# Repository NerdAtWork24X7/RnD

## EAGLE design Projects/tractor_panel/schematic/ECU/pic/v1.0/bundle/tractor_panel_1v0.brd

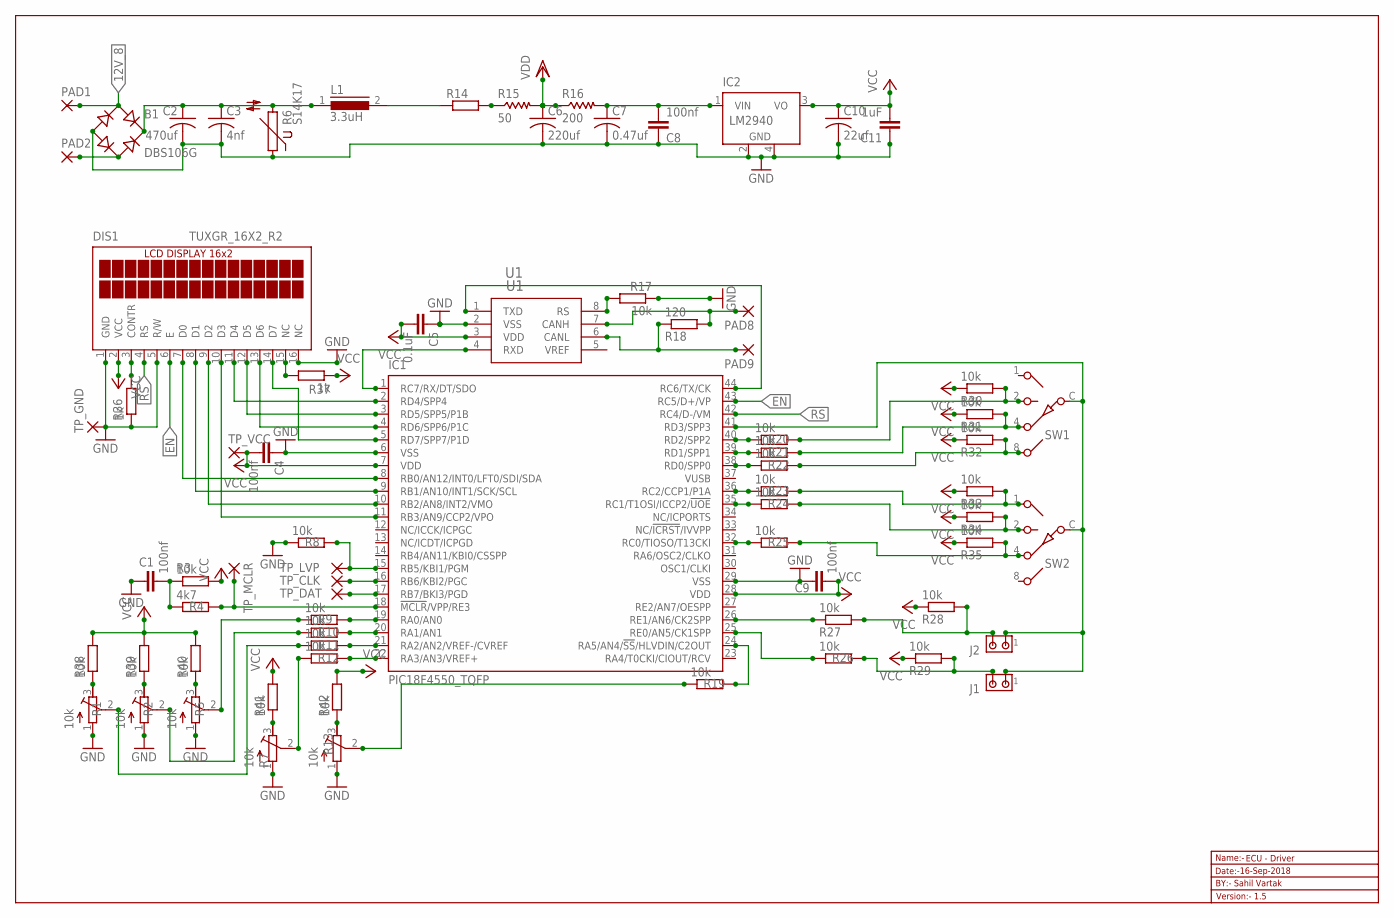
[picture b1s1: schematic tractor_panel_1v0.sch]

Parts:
B1: DBS106G; DBS
C1, C4, C8, C9: 100nf; C0603
C2: 470uf; C050-075X075
C3: 4nf; C050-045X075
C5: 0.1uF; C0603
C6: 220uf; C025-025X050
C7: 0.47uf; C025-025X050
C10: 22uf; C025-025X050
C11: 1uF; C0603
DIS1: TUXGR_16X2_R2
IC1: PIC18F4550_TQFP; TQFP44
IC2: LM2940; SOT223
J1, J2: MTA02-156; 1X2MTA
L1: 3.3uH; 82114R
PAD1, PAD2, PAD8, PAD9: 2,54/1,1
R1, R2, R5, R7, R13: 10k; RTRIM3296W
R3, R8, R9, R10, R11, R12, R17, R19, R20, R21, R22, R23, R24, R25, R26, R27, R28, R29, R30, R31, R32, R33, R34, R35, R38, R39, R40, R41, R42: 10k; R0603
R4: 4k7; R0603
R6: S14K17
R14: R-EU_R0603; R0603
R15: 50; WSC2515
R16: 200; WSC2515
R18: 120; R0603
R36, R37: 1k; R0603
SW1, SW2: SW-C10
TP_CLK: 1,6/0,8
TP_DAT: 1,6/0,8
TP_GND: 1,6/0,8
TP_LVP: 1,6/0,8
TP_MCLR: 1,6/0,8
TP_VCC: 1,6/0,8
U1: U1; SOIC8-N_MC-M

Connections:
12V_8: B1.AC1, PAD1.1
EN: DIS1.6 (E), IC1.43 (RC5/D+/VP)
GND: B1.-, C1.1, C2.2, C3.2, C4.1, C5.1, C6.2, C7.2, C8.1, C9.1, C10.2, C11.1, DIS1.1 (GND), DIS1.5 (R/W), DIS1.16 (NC), IC1.6 (VSS), IC1.29 (VSS), IC2.2 (GND), IC2.4 (GND), R1.1 (A), R2.1 (A), R5.1 (A), R6.1, R7.1 (A), R8.1, R13.1 (A), R17.1, R36.1, TP_GND.1, U1.2 (VSS)
unnamed: B1.AC2, PAD2.1
unnamed: DIS1.7 (D0), IC1.8 (RB0/AN12/INT0/LFT0/SDI/SDA)
unnamed: L1.2, R14.1
unnamed: DIS1.8 (D1), IC1.9 (RB1/AN10/INT1/SCK/SCL)
unnamed: R13.2 (S), R19.1
unnamed: DIS1.9 (D2), IC1.10 (RB2/AN8/INT2/VMO)
unnamed: C7.1, C8.2, IC2.1 (VIN), R16.2
unnamed: DIS1.3 (CONTR), R36.2
unnamed: DIS1.15 (NC), R37.2
unnamed: DIS1.10 (D3), IC1.11 (RB3/AN9/CCP2/VPO)
unnamed: DIS1.11 (D4), IC1.2 (RD4/SPP4)
unnamed: DIS1.14 (D7), IC1.5 (RD7/SPP7/P1D)
unnamed: R1.3 (E), R38.1
unnamed: R2.3 (E), R39.1
unnamed: R14.2, R15.1
unnamed: R5.3 (E), R40.1
unnamed: R7.3 (E), R41.1
unnamed: R13.3 (E), R42.1
unnamed: IC1.41 (RD3/SPP3), J1.1, J2.1, SW1.C, SW2.C
unnamed: B1.+, C2.1, C3.1, L1.1, R6.2
unnamed: DIS1.13 (D6), IC1.4 (RD6/SPP6/P1C)
unnamed: DIS1.12 (D5), IC1.3 (RD5/SPP5/P1B)
unnamed: PAD9.1, R18.1, U1.6 (CANL)
unnamed: PAD8.1, R18.2, U1.7 (CANH)
unnamed: IC1.1 (RC7/RX/DT/SDO), U1.4 (RXD)
unnamed: IC1.44 (RC6/TX/CK), U1.1 (TXD)
unnamed: R17.2, U1.8 (RS)
unnamed: J2.2, R27.2, R28.2
unnamed: IC1.26 (RE1/AN6/CK2SPP), R27.1
unnamed: IC1.32 (RC0/TIOSO/T13CKI), R25.1
unnamed: IC1.35 (RC1/T1OSI/ICCP2/!UOE), R24.1
unnamed: IC1.36 (RC2/CCP1/P1A), R23.1
unnamed: IC1.38 (RD0/SPP0), R22.1
unnamed: IC1.39 (RD1/SPP1), R21.1
unnamed: IC1.40 (RD2/SPP2), R20.1
unnamed: R20.2, R30.2, SW1.2
unnamed: R21.2, R31.2, SW1.4
unnamed: R22.2, R32.2, SW1.8
unnamed: R23.2, R33.2, SW2.1
unnamed: R24.2, R34.2, SW2.2
unnamed: R25.2, R35.2, SW2.4
unnamed: IC1.25 (RE0/AN5/CK1SPP), R26.1
unnamed: IC1.17 (RB7/BKI3/PGD), TP_DAT.1
unnamed: IC1.16 (RB6/KBI2/PGC), TP_CLK.1
unnamed: J1.2, R26.2, R29.2
unnamed: IC1.22 (RA3/AN3/VREF+), R12.2
unnamed: IC1.21 (RA2/AN2/VREF-/CVREF), R11.2
unnamed: IC1.20 (RA1/AN1), R10.2
unnamed: IC1.19 (RA0/AN0), R9.2
unnamed: R5.2 (S), R9.1
unnamed: R2.2 (S), R10.1
unnamed: R1.2 (S), R11.1
unnamed: R7.2 (S), R12.1
unnamed: IC1.24 (RA5/AN4/!SS!/HLVDIN/C2OUT), R19.2
unnamed: C1.2, R3.1, R4.1
unnamed: IC1.18 (!MCLR!/VPP/RE3), R4.2, TP_MCLR.1
unnamed: IC1.15 (RB5/KBI1/PGM), R8.2, TP_LVP.1
RS: DIS1.4 (RS), IC1.42 (RC4/D-/VM)
VCC: C4.2, C5.2, C9.2, C10.1, C11.2, DIS1.2 (VCC), IC1.7 (VDD), IC1.28 (VDD), IC2.3 (VO), R3.2, R28.1, R29.1, R30.1, R31.1, R32.1, R33.1, R34.1, R35.1, R37.1, R38.2, R39.2, R40.2, R41.2, R42.2, TP_VCC.1, U1.3 (VDD)
VDD: C6.1, R15.2, R16.1

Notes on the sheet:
Name:-
Version:- 1.5
Date:-
ECU - Driver
BY:- Sahil Vartak
16-Sep-2018

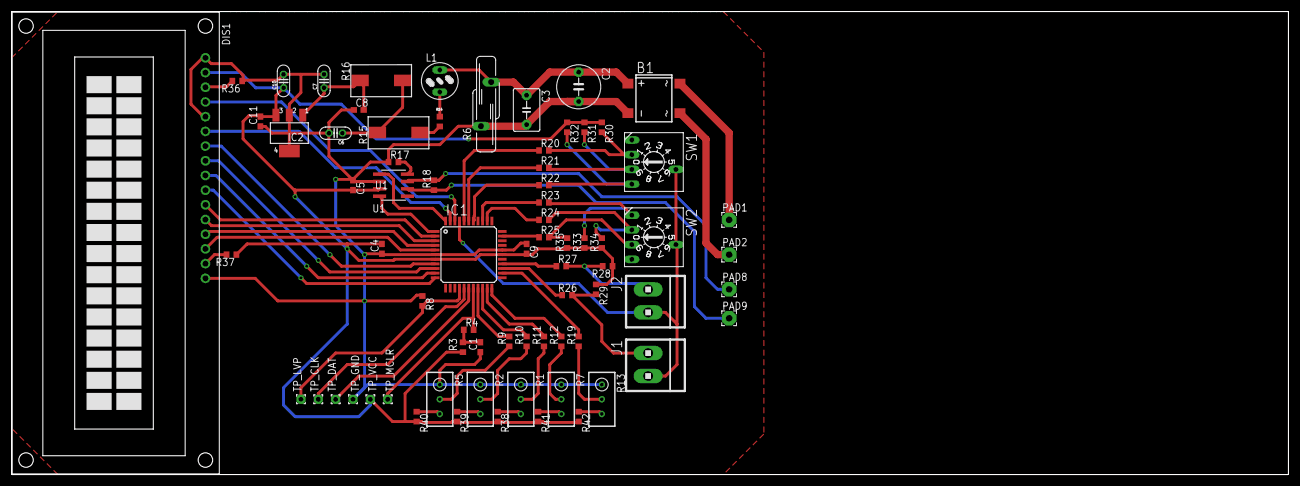
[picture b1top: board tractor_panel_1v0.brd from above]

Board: 2 copper layers, 220.7 x 80.0 mm, 73 parts (0 on the bottom side), 63 nets.

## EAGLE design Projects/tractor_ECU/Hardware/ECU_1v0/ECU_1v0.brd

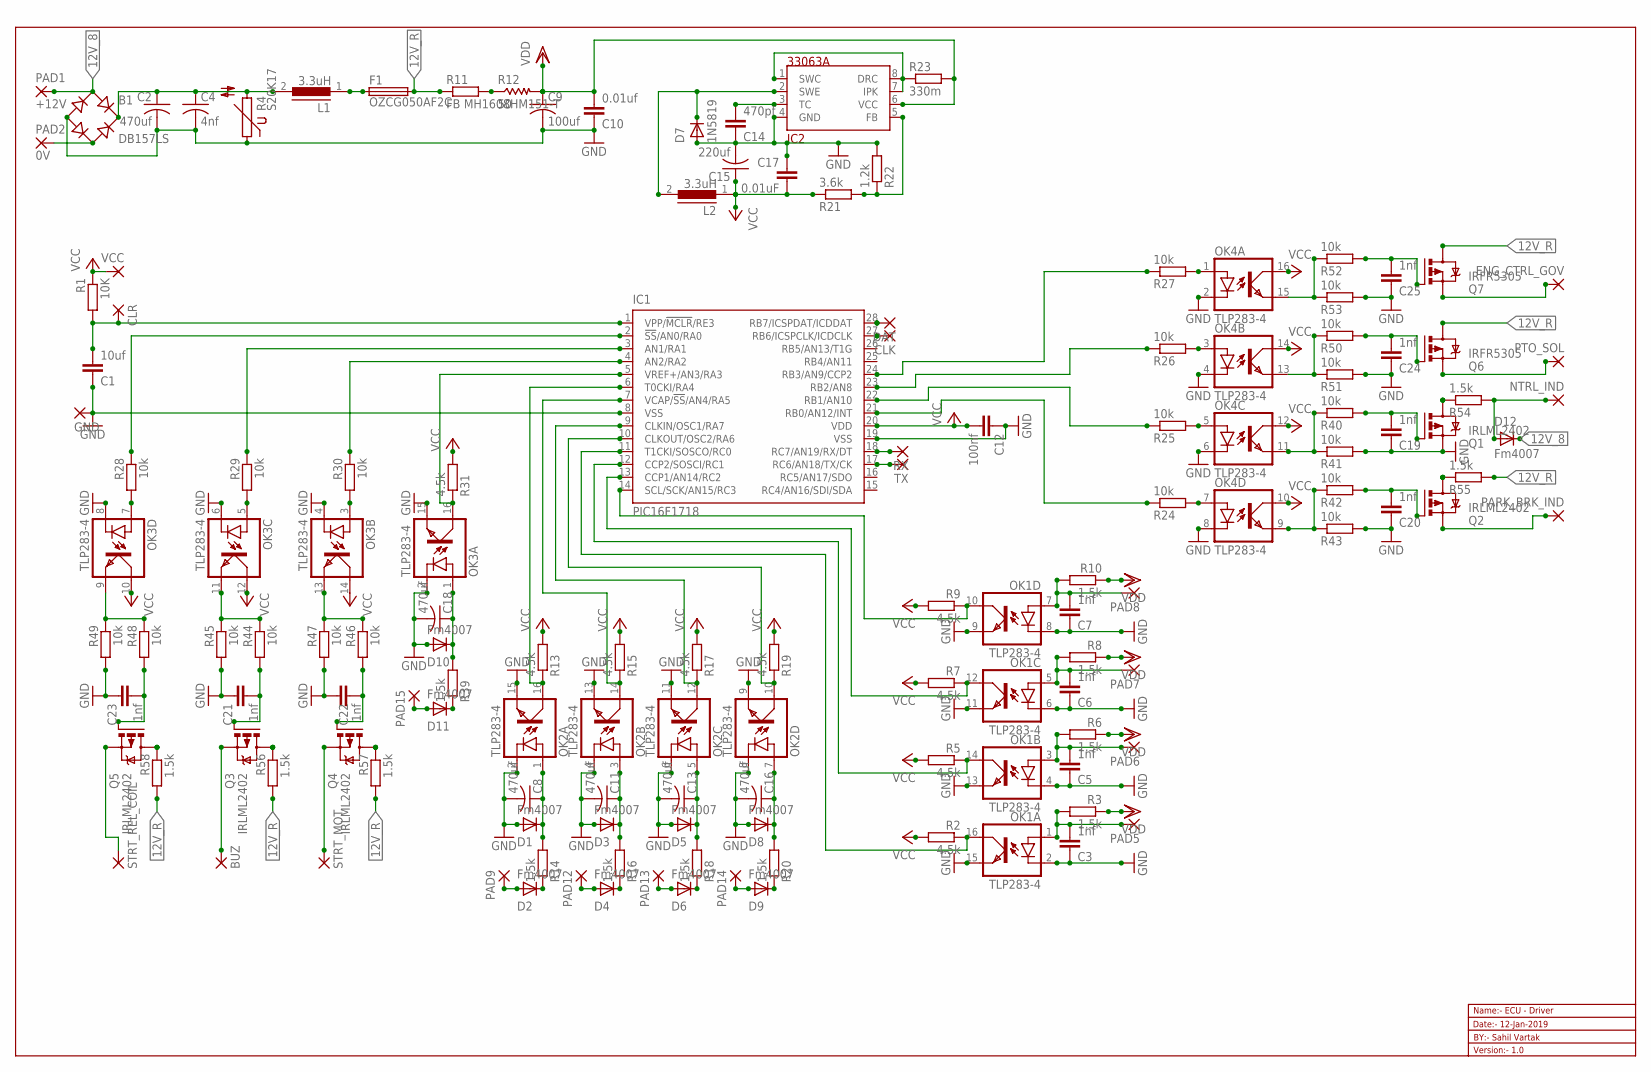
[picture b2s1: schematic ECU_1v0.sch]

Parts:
B1: DB157LS; DBS
BUZ: 2,54/1,1
C1: 10uf; C0603
C2, C8, C11, C13, C16, C18: 470uf; C050-075X075
C3, C5, C6, C7, C19, C20, C21, C22, C23, C24, C25: 1nf; C0603
C4: 4nf; C050-045X075
C9: 100uf; C025-025X050
C10: 0.01uf; C0603
C12: 100nf; C0603
C14: 470pf; C0603
C15: 220uf; C025-025X050
C17: 0.01uF; C0603
CLK: 1,6/0,8
CLR: 1,6/0,8
D1, D2, D3, D4, D5, D6, D8, D9, D10, D11, D12: Fm4007; SMA-DO214AC
D7: 1N5819; SMA-DO214AC
DAT: 1,6/0,8
ENG_CTRL_GOV: 2,54/1,1
F1: OZCG050AF2C; RES_FUSE
GND: 1,6/0,8
IC1: PIC16F1718; SO28W
IC2: 33063A; D_R-PDSO-G8
L1, L2: 3.3uH; 82114R
NTRL_IND: 2,54/1,1
OK1, OK2, OK3, OK4: TLP283-4; MINI-FLAT-16
PAD1: +12V; 2,54/1,1
PAD2: 0V; 2,54/1,1
PAD5, PAD6, PAD7, PAD8, PAD9, PAD12, PAD13, PAD14, PAD15: 2,54/1,1
PARK_BRK_IND: 2,54/1,1
PTO_SOL: 2,54/1,1
Q1, Q2, Q3, Q4, Q5: IRLML2402; MICRO3
Q6, Q7: IRFR5305; D-PAK_TO252AA
R1: 10K; R0603
R2, R5, R7, R9, R13, R15, R17, R19, R31: 4.5k; R0603
R3, R6, R8, R10, R14, R16, R18, R20, R39, R54, R55, R56, R57, R58: 1.5k; R0603
R4: S20K17; S14K17
R11: FB MH1608HM151-T; R0603
R12: 50; WSC2515
R21: 3.6k; R0603
R22: 1.2k; R0603
R23: 330m; R2010
R24, R25, R26, R27, R28, R29, R30, R40, R41, R42, R43, R44, R45, R46, R47, R48, R49, R50, R51, R52, R53: 10k; R0603
RX: 1,6/0,8
STRT_MOT: 2,54/1,1
STRT_REL_COIL: 2,54/1,1
TX: 1,6/0,8
VCC: 1,6/0,8

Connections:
12V_8: B1.AC1, D12.K (C), PAD1.1
12V_R: F1.2 (4), Q6.4 (D), Q7.4 (D), R11.1, R55.2, R56.2, R57.2, R58.2
GND: B1.-, C1.1, C2.2, C3.1, C4.2, C5.1, C6.1, C7.1, C8.2, C9.2, C10.1, C11.2, C12.1, C13.2, C14.1, C15.2, C16.2, C17.1, C18.2, C19.1, C20.1, C21.1, C22.1, C23.1, C24.1, C25.1, D1.A, D3.A, D5.A, D7.A, D8.A, D10.A, GND.1, IC1.8 (VSS), IC1.19 (VSS), IC2.4 (GND), OK1.2 (C), OK1.4 (C), OK1.6 (C), OK1.8 (C), OK1.9 (EMIT), OK1.11 (EMIT), OK1.13 (EMIT), OK1.15 (EMIT), OK2.2 (C), OK2.4 (C), OK2.6 (C), OK2.8 (C), OK2.9 (EMIT), OK2.11 (EMIT), OK2.13 (EMIT), OK2.15 (EMIT), OK3.2 (C), OK3.4 (C), OK3.6 (C), OK3.8 (C), OK3.15 (EMIT), OK4.2 (C), OK4.4 (C), OK4.6 (C), OK4.8 (C), Q1.2 (S), R4.1, R22.2, R41.2, R43.2, R45.2, R47.2, R49.2, R51.2, R53.2
unnamed: IC1.4 (AN2/RA2), R30.1
unnamed: IC1.21 (RB0/AN12/INT), R24.1
unnamed: PARK_BRK_IND.1, Q2.2 (S)
unnamed: IC1.10 (CLKOUT/OSC2/RA6), OK2.10 (COL), R19.1
unnamed: IC1.11 (T1CKI/SOSCO/RC0), OK1.16 (COL), R2.1
unnamed: IC1.23 (RB2/AN8), R26.1
unnamed: IC1.13 (CCP1/AN14/RC2), OK1.12 (COL), R7.1
unnamed: IC1.14 (SCL/SCK/AN15/RC3), OK1.10 (COL), R9.1
unnamed: C1.2, CLR.1, IC1.1 (VPP/!MCLR!/RE3), R1.2
unnamed: R11.2, R12.1
unnamed: IC1.24 (RB3/AN9/CCP2), R27.1
unnamed: IC1.22 (RB1/AN10), R25.1
unnamed: IC2.1 (SWC), IC2.7 (IPK), IC2.8 (DRC), R23.1
unnamed: C14.2, IC2.3 (TC)
unnamed: BUZ.1, Q3.2 (S)
unnamed: F1.1 (3), L1.1
unnamed: D7.K (C), IC2.2 (SWE), L2.2
unnamed: IC2.5 (FB), R21.2, R22.1
unnamed: Q4.2 (S), STRT_MOT.1
unnamed: Q5.2 (S), STRT_REL_COIL.1
unnamed: PTO_SOL.1, Q6.3 (S)
unnamed: ENG_CTRL_GOV.1, Q7.3 (S)
unnamed: IC1.18 (RC7/AN19/RX/DT), RX.1
unnamed: B1.+, C2.1, C4.1, L1.2, R4.2
unnamed: IC1.17 (RC6/AN18/TX/CK), TX.1
unnamed: C3.2, OK1.1 (A), PAD5.1, R3.2
unnamed: B1.AC2, PAD2.1
unnamed: C5.2, OK1.3 (A), PAD6.1, R6.2
unnamed: C6.2, OK1.5 (A), PAD7.1, R8.2
unnamed: C7.2, OK1.7 (A), PAD8.1, R10.2
unnamed: C8.1, D1.K (C), OK2.1 (A), R14.2
unnamed: D2.K (C), R14.1
unnamed: D2.A, PAD9.1
unnamed: C11.1, D3.K (C), OK2.3 (A), R16.2
unnamed: D4.K (C), R16.1
unnamed: D4.A, PAD12.1
unnamed: C13.1, D5.K (C), OK2.5 (A), R18.2
unnamed: D6.K (C), R18.1
unnamed: D6.A, PAD13.1
unnamed: C16.1, D8.K (C), OK2.7 (A), R20.2
unnamed: D9.K (C), R20.1
unnamed: D9.A, PAD14.1
unnamed: C18.1, D10.K (C), OK3.1 (A), R39.2
unnamed: D11.K (C), R39.1
unnamed: D11.A, PAD15.1
unnamed: OK4.7 (A), R24.2
unnamed: OK4.5 (A), R25.2
unnamed: OK4.3 (A), R26.2
unnamed: OK4.1 (A), R27.2
unnamed: OK3.7 (A), R28.2
unnamed: OK3.5 (A), R29.2
unnamed: OK3.3 (A), R30.2
unnamed: IC1.2 (!SS!/AN0/RA0), R28.1
unnamed: IC1.3 (AN1/RA1), R29.1
unnamed: IC1.5 (VREF+/AN3/RA3), OK3.16 (COL), R31.1
unnamed: IC1.6 (T0CKI/RA4), OK2.16 (COL), R13.1
unnamed: IC1.7 (VCAP/!SS!/AN4/RA5), OK2.14 (COL), R15.1
unnamed: IC1.9 (CLKIN/OSC1/RA7), OK2.12 (COL), R17.1
unnamed: IC1.12 (CCP2/SOSCI/RC1), OK1.14 (COL), R5.1
unnamed: C19.2, Q1.1 (G), R40.2
unnamed: C20.2, Q2.1 (G), R42.2
unnamed: OK4.11 (EMIT), R40.1, R41.1
unnamed: OK4.9 (EMIT), R42.1, R43.1
unnamed: C21.2, Q3.1 (G), R44.2
unnamed: OK3.11 (EMIT), R44.1, R45.1
unnamed: C22.2, Q4.1 (G), R46.2
unnamed: OK3.13 (EMIT), R46.1, R47.1
unnamed: C23.2, Q5.1 (G), R48.2
unnamed: OK3.9 (EMIT), R48.1, R49.1
unnamed: C24.2, Q6.1 (G), R50.2
unnamed: OK4.13 (EMIT), R50.1, R51.1
unnamed: C25.2, Q7.1 (G), R52.2
unnamed: OK4.15 (EMIT), R52.1, R53.1
unnamed: Q1.3 (D), R54.1
unnamed: Q2.3 (D), R55.1
unnamed: Q3.3 (D), R56.1
unnamed: Q4.3 (D), R57.1
unnamed: Q5.3 (D), R58.1
unnamed: D12.A, NTRL_IND.1, R54.2
unnamed: DAT.1, IC1.28 (RB7/ICSPDAT/ICDDAT)
unnamed: CLK.1, IC1.27 (RB6/ICSPCLK/ICDCLK)
VCC: C12.2, C15.1, C17.2, IC1.20 (VDD), L2.1, OK3.10 (COL), OK3.12 (COL), OK3.14 (COL), OK4.10 (COL), OK4.12 (COL), OK4.14 (COL), OK4.16 (COL), R1.1, R2.2, R5.2, R7.2, R9.2, R13.2, R15.2, R17.2, R19.2, R21.1, R31.2, VCC.1
VDD: C9.1, C10.2, IC2.6 (VCC), R3.1, R6.1, R8.1, R10.1, R12.2, R23.2

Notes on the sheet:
Name:- ECU - Driver
Version:- 1.0
Date:- 12-Jan-2019
BY:- Sahil Vartak

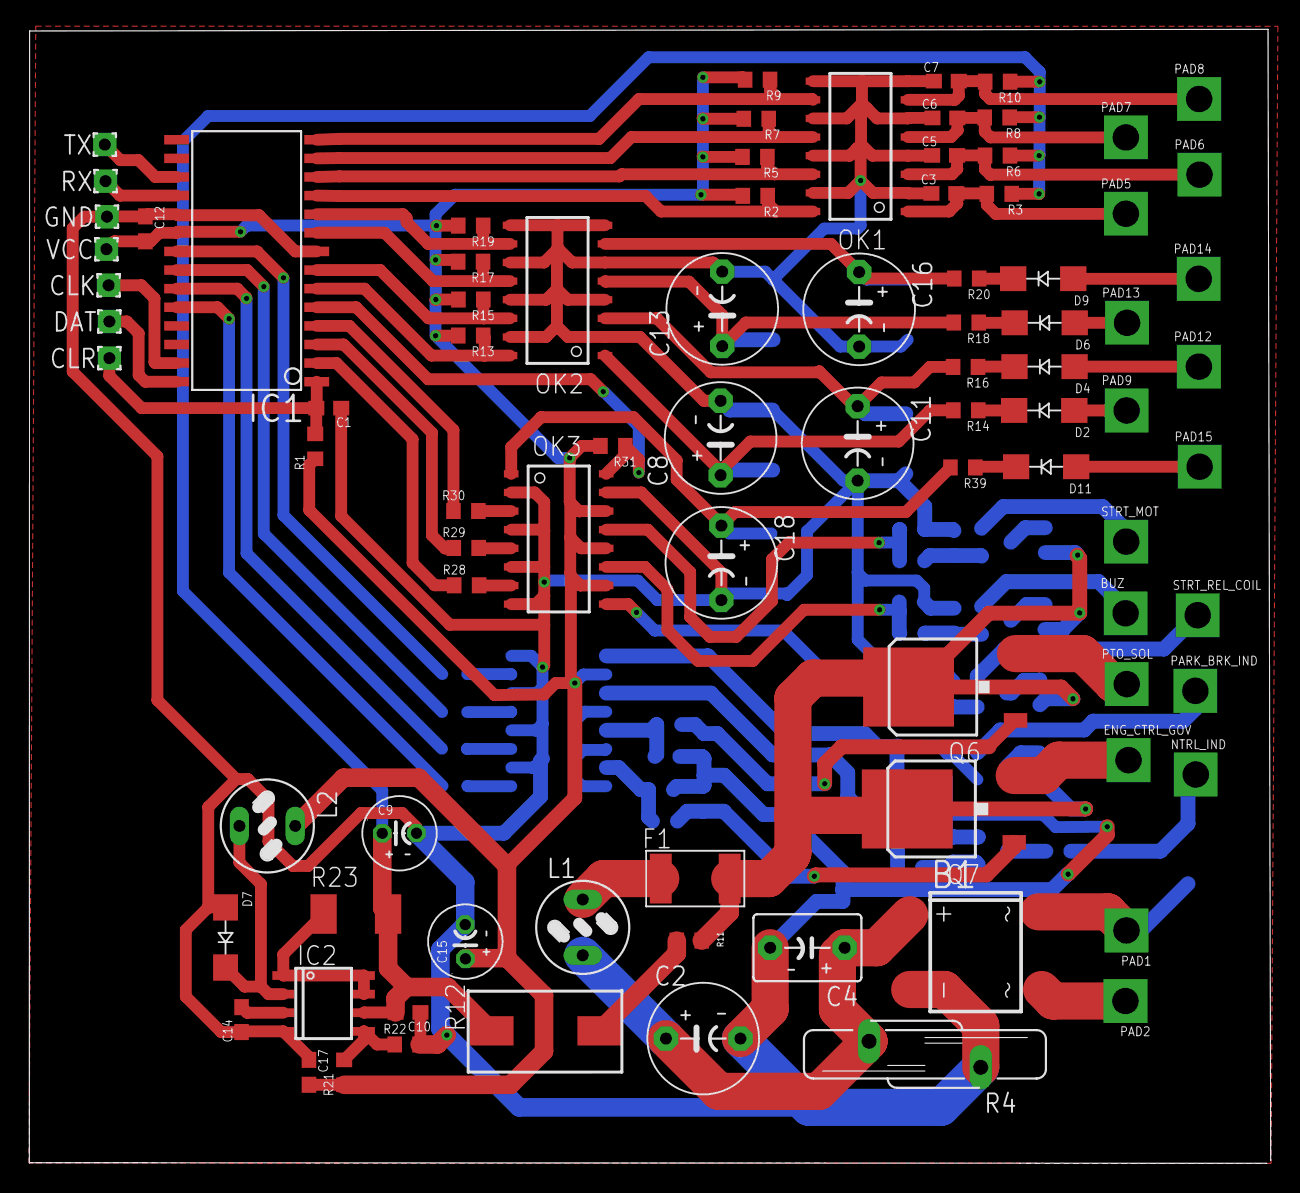
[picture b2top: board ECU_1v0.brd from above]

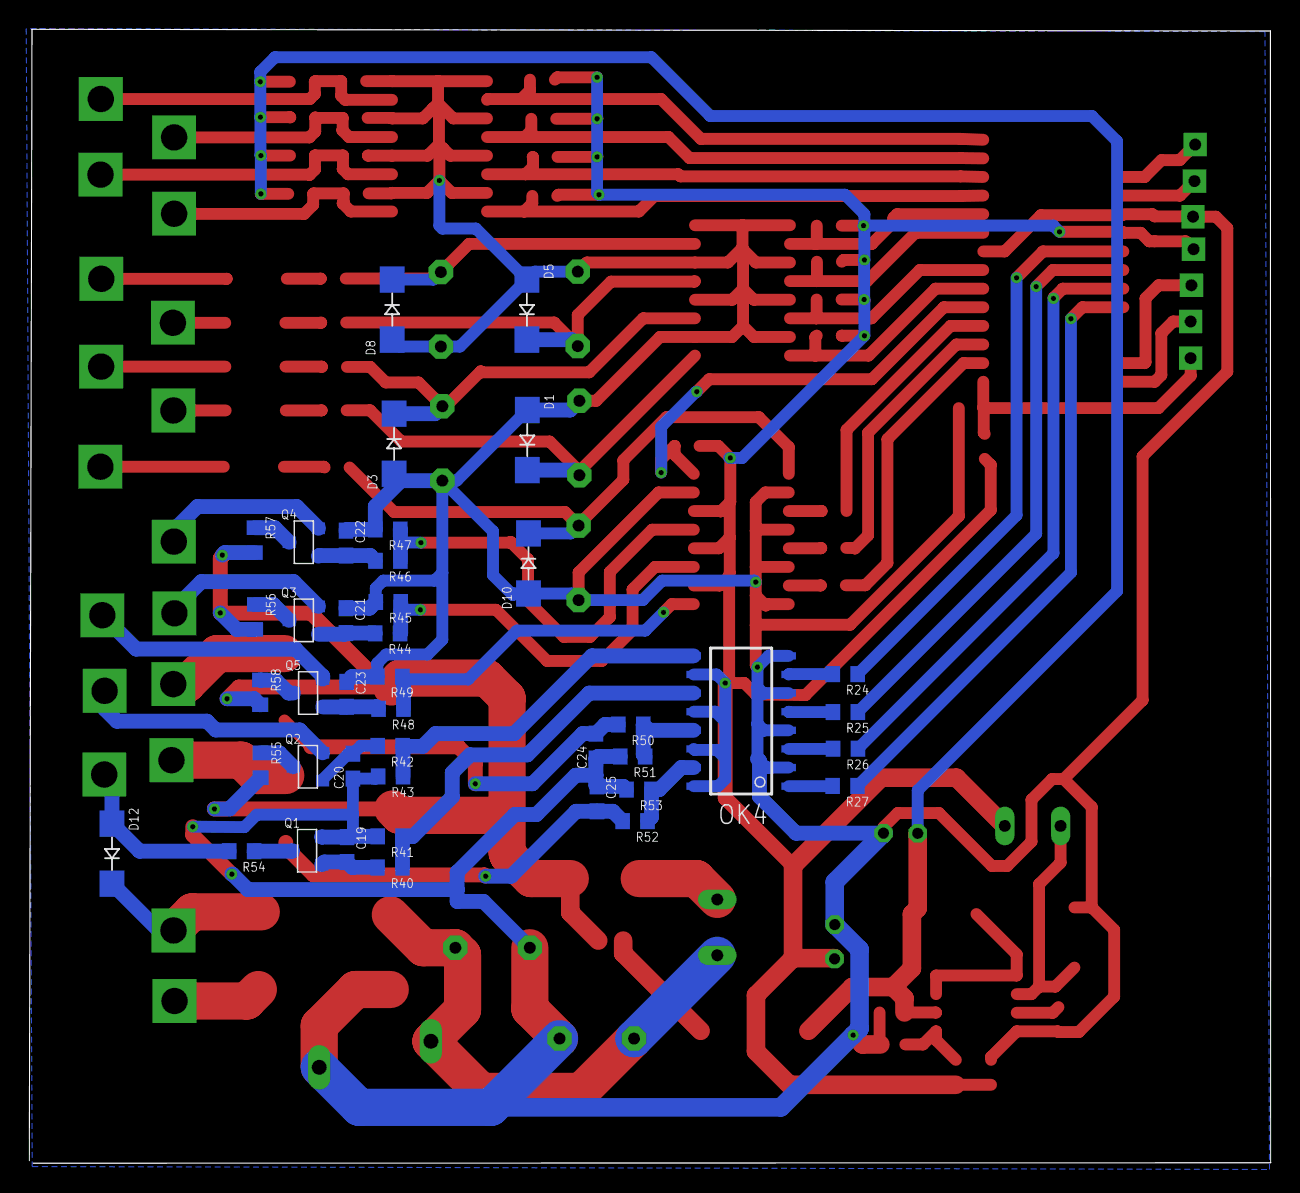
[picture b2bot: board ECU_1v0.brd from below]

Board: 2 copper layers, 84.7 x 77.4 mm, 130 parts (42 on the bottom side), 86 nets.

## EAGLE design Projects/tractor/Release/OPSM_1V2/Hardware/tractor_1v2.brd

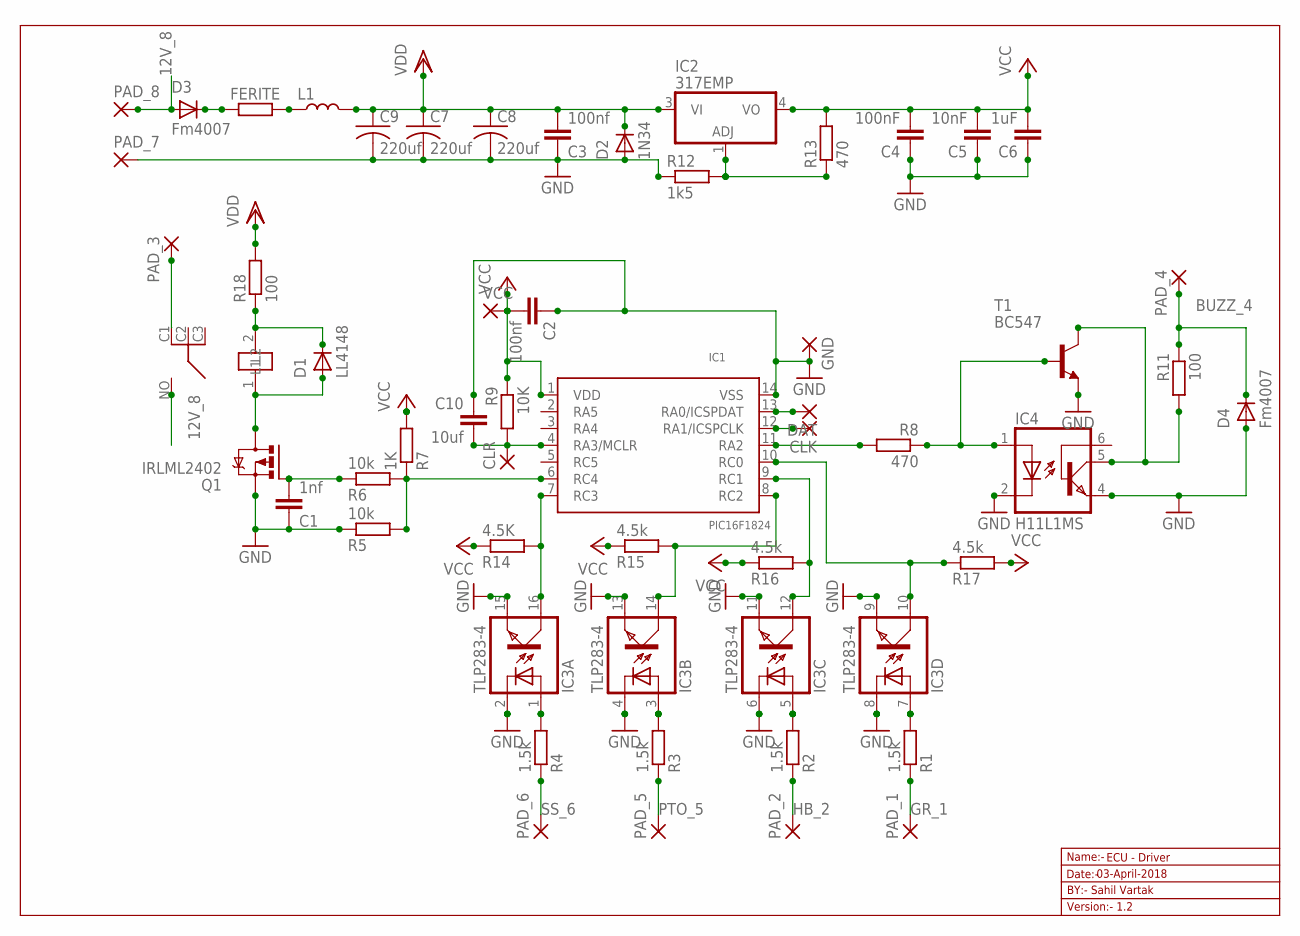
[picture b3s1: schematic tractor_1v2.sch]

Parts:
C1: 1nf; C0603
C2, C3: 100nf; C0603
C4: 100nF; C0603
C5: 10nF; C0603
C6: 1uF; C0603
C7, C8, C9: 220uf; C025-025X050
C10: 10uf; C0603
CLK: 1,6/0,8
CLR: 1,6/0,8
D1: LL4148; SMA-DO214AC
D2: 1N34; SMA-DO214AC
D3, D4: Fm4007; SMA-DO214AC
DAT: 1,6/0,8
FERITE: R-EU_R0603; R0603
GND: 1,6/0,8
IC1: PIC16F1824; SO-14
IC2: 317EMP; SOT223
IC3: TLP283-4; MINI-FLAT-16
IC4: H11L1MS; DIL6-SMD
K2: RL703
L1: R-US_WSC2515; WSC2515
PAD_1, PAD_2, PAD_3, PAD_4, PAD_5, PAD_6, PAD_7, PAD_8: 2,54/1,1
Q1: IRLML2402; MICRO3
R1, R2, R3, R4: 1.5k; R0603
R5, R6: 10k; R0603
R7: 1K; R0603
R8, R13: 470; R0603
R9: 10K; R0603
R11, R18: 100; R0603
R12: 1k5; R0603
R14: 4.5K; R0603
R15, R16, R17: 4.5k; R0603
T1: BC547; TO92
VCC: 1,6/0,8

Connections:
12V_8: D3.A, K2.NO, PAD_8.1
BUZZ_4: D4.K (C), PAD_4.1, R11.1
GND: C1.1, C2.1, C3.1, C4.1, C5.1, C6.1, C7.2, C8.2, C9.2, C10.1, D2.A, D4.A, GND.1, IC1.14 (VSS), IC3.2 (C), IC3.4 (C), IC3.6 (C), IC3.8 (C), IC3.9 (EMIT), IC3.11 (EMIT), IC3.13 (EMIT), IC3.15 (EMIT), IC4.2 (C), IC4.4 (EMI), PAD_7.1, Q1.2 (S), R5.1, R12.1, T1.1 (E)
GR_1: PAD_1.1, R1.1
HB_2: PAD_2.1, R2.1
unnamed: IC1.10 (RC0), IC3.10 (COL), R17.1
unnamed: D1.A, K2.1 (L2), Q1.3 (D)
unnamed: D3.K (C), FERITE.1
unnamed: DAT.1, IC1.13 (RA0/ICSPDAT)
unnamed: CLK.1, IC1.12 (RA1/ICSPCLK)
unnamed: D1.K (C), K2.2 (L1), R18.1
unnamed: IC2.1 (ADJ), R12.2, R13.1
unnamed: FERITE.2, L1.1
unnamed: C1.2, Q1.1 (G), R6.1
unnamed: IC1.6 (RC4), R5.2, R6.2, R7.1
unnamed: IC3.1 (A), R4.2
unnamed: IC3.3 (A), R3.2
unnamed: IC3.5 (A), R2.2
unnamed: IC3.7 (A), R1.2
unnamed: IC1.9 (RC1), IC3.12 (COL), R16.2
unnamed: IC1.8 (RC2), IC3.14 (COL), R15.2
unnamed: IC1.7 (RC3), IC3.16 (COL), R14.2
unnamed: C10.2, CLR.1, IC1.4 (RA3/MCLR), R9.2
unnamed: IC1.11 (RA2), R8.2
unnamed: IC4.1 (A), R8.1, T1.2 (B)
unnamed: IC4.5 (COL), R11.2, T1.3 (C)
PTO_5: PAD_5.1, R3.1
R_3: K2.C1, PAD_3.1
SS_6: PAD_6.1, R4.1
VCC: C2.2, C4.2, C5.2, C6.2, IC1.1 (VDD), IC2.4 (VO), R7.2, R9.1, R13.2, R14.1, R15.1, R16.1, R17.2, VCC.1
VDD: C3.2, C7.1, C8.1, C9.1, D2.K (C), IC2.3 (VI), L1.2, R18.2

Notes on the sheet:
Name:-
Version:- 1.2
Date:-
ECU - Driver
BY:- Sahil Vartak
03-April-2018

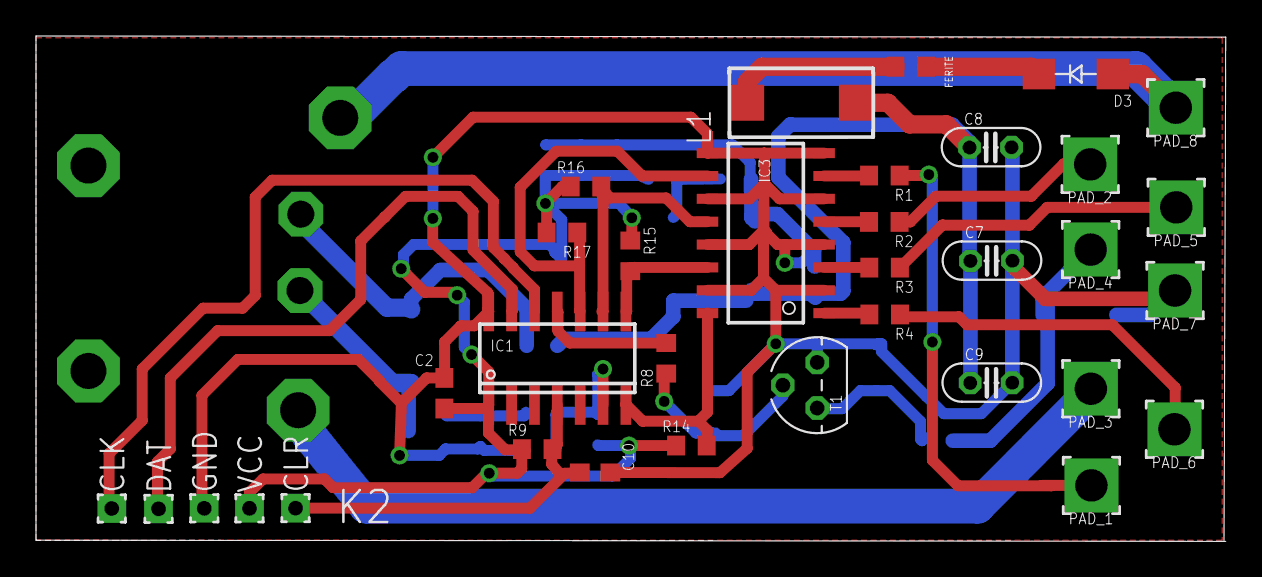
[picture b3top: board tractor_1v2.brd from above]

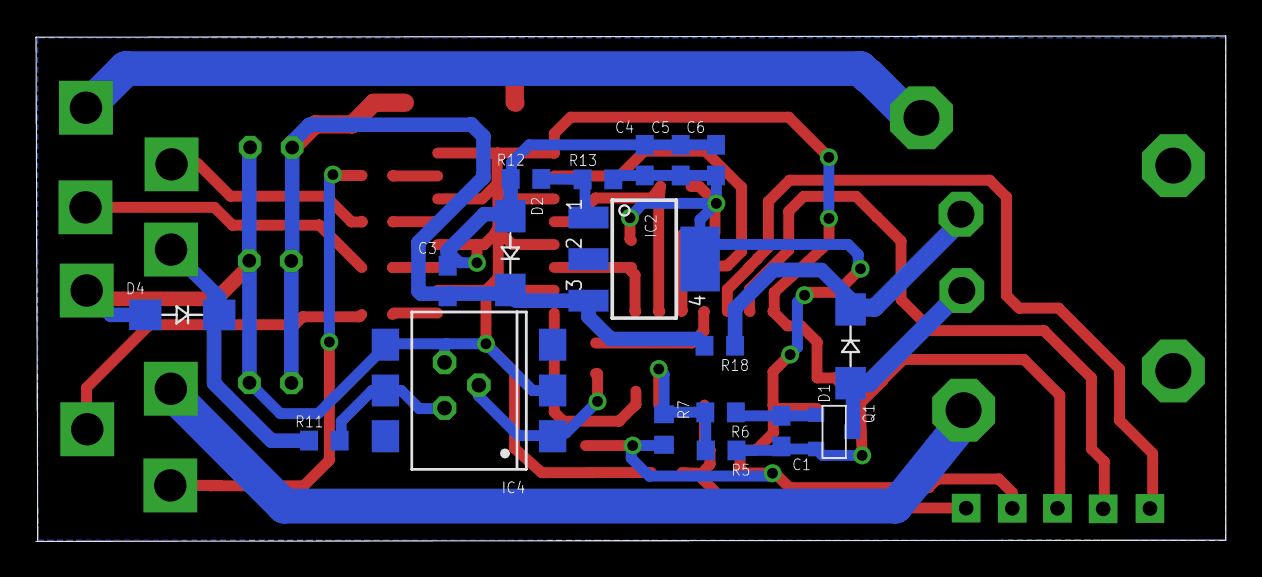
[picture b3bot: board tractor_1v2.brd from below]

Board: 2 copper layers, 66.1 x 28.1 mm, 53 parts (19 on the bottom side), 31 nets.

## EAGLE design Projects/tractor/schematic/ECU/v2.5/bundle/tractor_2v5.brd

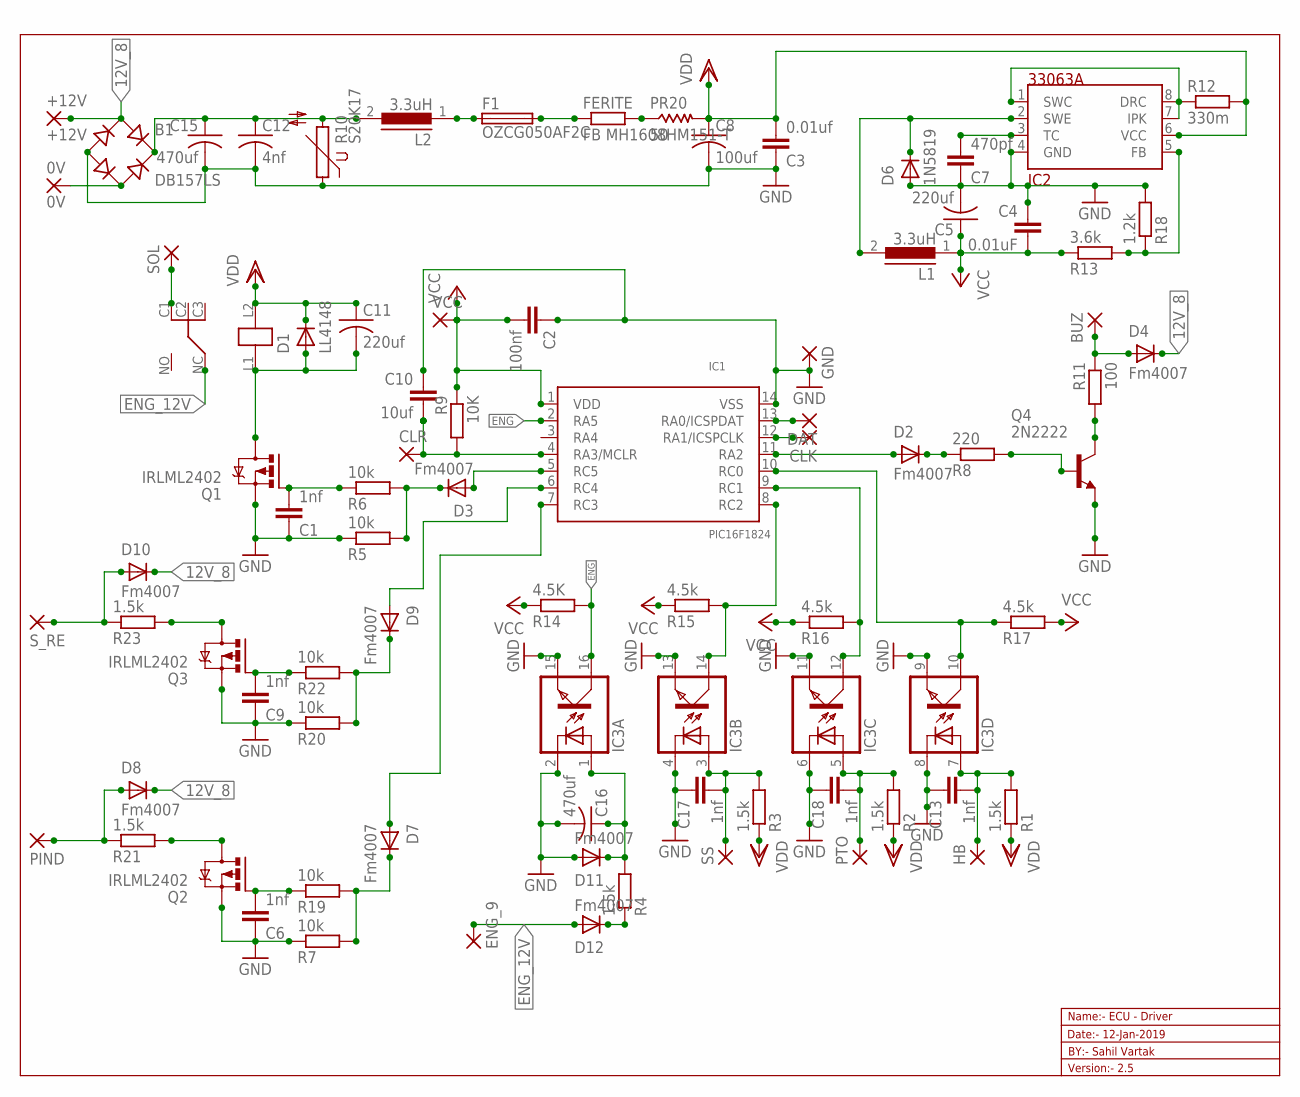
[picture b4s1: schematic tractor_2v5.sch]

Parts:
0V: 0V; 2,54/1,1
+12V: +12V; 2,54/1,1
B1: DB157LS; DBS
BUZ: 2,54/1,1
C1, C6, C9, C13, C17, C18: 1nf; C0603
C2: 100nf; C0603
C3: 0.01uf; C0603
C4: 0.01uF; C0603
C5, C11: 220uf; C025-025X050
C7: 470pf; C0603
C8: 100uf; C025-025X050
C10: 10uf; C0603
C12: 4nf; C050-045X075
C15, C16: 470uf; C050-075X075
CLK: 1,6/0,8
CLR: 1,6/0,8
D1: LL4148; SMA-DO214AC
D2, D3, D4, D7, D8, D9, D10, D11, D12: Fm4007; SMA-DO214AC
D6: 1N5819; SMA-DO214AC
DAT: 1,6/0,8
ENG_9: 2,54/1,1
F1: OZCG050AF2C; RES_FUSE
FERITE: FB MH1608HM151-T; R0603
GND: 1,6/0,8
HB: 2,54/1,1
IC1: PIC16F1824; SO-14
IC2: 33063A; D_R-PDSO-G8
IC3: TLP283-4; MINI-FLAT-16
K2: RL3531RL3; RL3531
L1, L2: 3.3uH; 82114R
PIND: 2,54/1,1
PR20: 50; WSC2515
PTO: 2,54/1,1
Q1, Q2, Q3: IRLML2402; MICRO3
Q4: 2N2222; TO18
R1, R2, R3, R4, R21, R23: 1.5k; R0603
R5, R6, R7, R19, R20, R22: 10k; R0603
R8: 220; R0603
R9: 10K; R0603
R10: S20K17; S14K17
R11: 100; R0603
R12: 330m; R2010
R13: 3.6k; R0603
R14: 4.5K; R0603
R15, R16, R17: 4.5k; R0603
R18: 1.2k; R0603
SOL: 2,54/1,1
SS: 2,54/1,1
S_RE: 2,54/1,1
VCC: 1,6/0,8

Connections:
12V_8: +12V.1, B1.AC1, D4.K (C), D8.K (C), D10.K (C)
ENG: IC1.2 (RA5), IC3.16 (COL), R14.2
ENG_12V: D12.A, ENG_9.1, K2.NC
GND: B1.-, C1.1, C2.1, C3.1, C4.1, C5.2, C6.1, C7.1, C8.2, C9.1, C10.1, C12.2, C13.1, C15.2, C16.2, C17.1, C18.1, D6.A, D11.A, GND.1, IC1.14 (VSS), IC2.4 (GND), IC3.2 (C), IC3.4 (C), IC3.6 (C), IC3.8 (C), IC3.9 (EMIT), IC3.11 (EMIT), IC3.13 (EMIT), IC3.15 (EMIT), Q1.2 (S), Q2.2 (S), Q3.2 (S), Q4.1 (E), R5.1, R7.1, R10.1, R18.2, R20.1
unnamed: Q4.2 (B), R8.2
unnamed: IC1.10 (RC0), IC3.10 (COL), R17.1
unnamed: C11.2, D1.A, K2.L1, Q1.3 (D)
unnamed: C9.2, Q3.1 (G), R22.1
unnamed: D2.K (C), R8.1
unnamed: DAT.1, IC1.13 (RA0/ICSPDAT)
unnamed: CLK.1, IC1.12 (RA1/ICSPCLK)
unnamed: Q4.3 (C), R11.2
unnamed: FERITE.2, PR20.1
unnamed: BUZ.1, D4.A, R11.1
unnamed: D3.A, IC1.5 (RC5)
unnamed: IC2.1 (SWC), IC2.7 (IPK), IC2.8 (DRC), R12.1
unnamed: C7.2, IC2.3 (TC)
unnamed: F1.2 (4), FERITE.1
unnamed: F1.1 (3), L2.1
unnamed: D6.K (C), IC2.2 (SWE), L1.2
unnamed: IC2.5 (FB), R13.2, R18.1
unnamed: C6.2, Q2.1 (G), R19.1
unnamed: Q2.3 (D), R21.2
unnamed: D7.K (C), R7.2, R19.2
unnamed: D9.A, IC1.6 (RC4)
unnamed: D8.A, PIND.1, R21.1
unnamed: B1.+, C12.1, C15.1, L2.2, R10.2
unnamed: D9.K (C), R20.2, R22.2
unnamed: D7.A, IC1.7 (RC3)
unnamed: Q3.3 (D), R23.2
unnamed: D10.A, R23.1, S_RE.1
unnamed: C18.2, IC3.5 (A), PTO.1, R2.2
unnamed: D12.K (C), R4.1
unnamed: 0V.1, B1.AC2
unnamed: C1.2, Q1.1 (G), R6.1
unnamed: D3.K (C), R5.2, R6.2
unnamed: C16.1, D11.K (C), IC3.1 (A), R4.2
unnamed: C17.2, IC3.3 (A), R3.2, SS.1
unnamed: C13.2, HB.1, IC3.7 (A), R1.2
unnamed: IC1.9 (RC1), IC3.12 (COL), R16.2
unnamed: IC1.8 (RC2), IC3.14 (COL), R15.2
unnamed: C10.2, CLR.1, IC1.4 (RA3/MCLR), R9.2
unnamed: D2.A, IC1.11 (RA2)
R_3: K2.C1, SOL.1
VCC: C2.2, C4.2, C5.1, IC1.1 (VDD), L1.1, R9.1, R13.1, R14.1, R15.1, R16.1, R17.2, VCC.1
VDD: C3.2, C8.1, C11.1, D1.K (C), IC2.6 (VCC), K2.L2, PR20.2, R1.1, R2.1, R3.1, R12.2

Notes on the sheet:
Name:- ECU - Driver
Version:- 2.5
Date:- 12-Jan-2019
BY:- Sahil Vartak

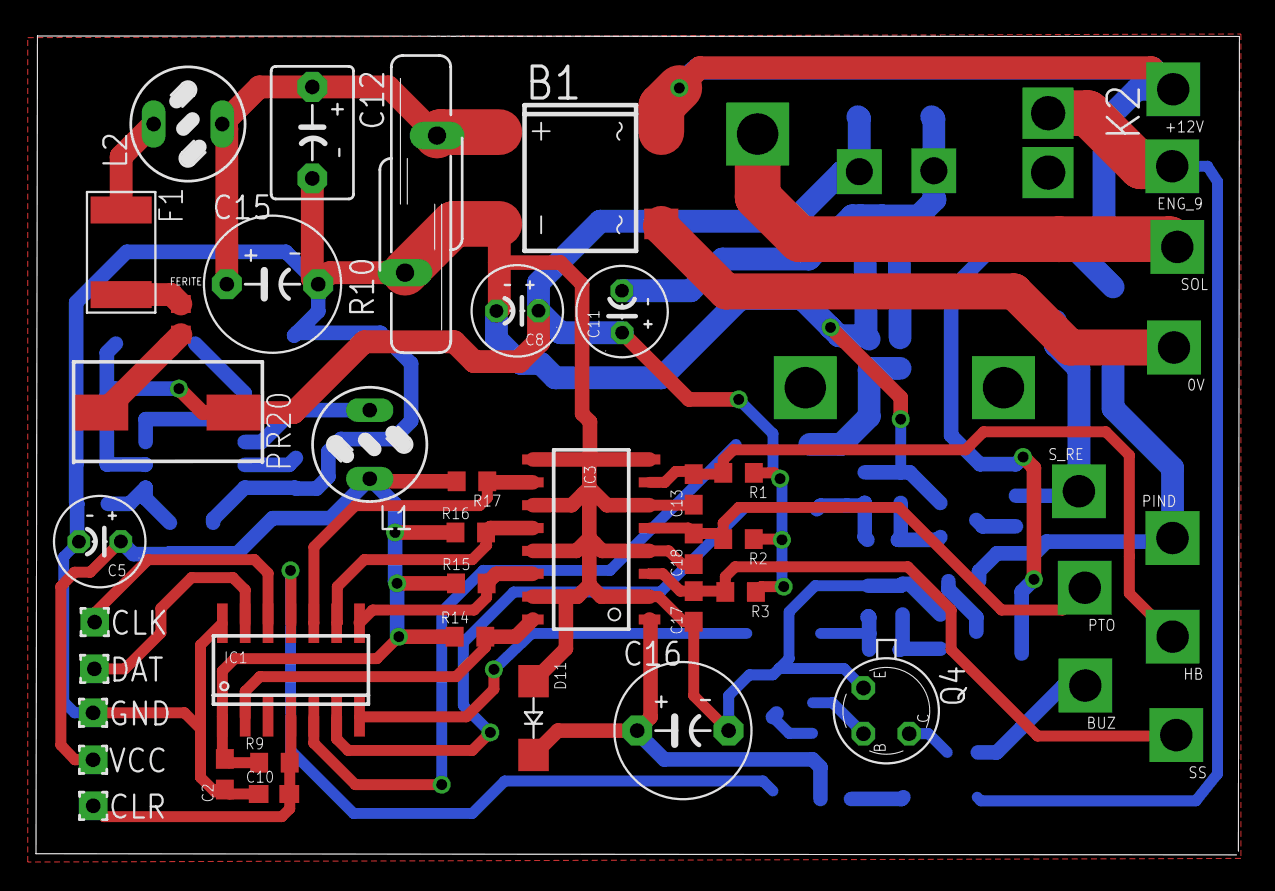
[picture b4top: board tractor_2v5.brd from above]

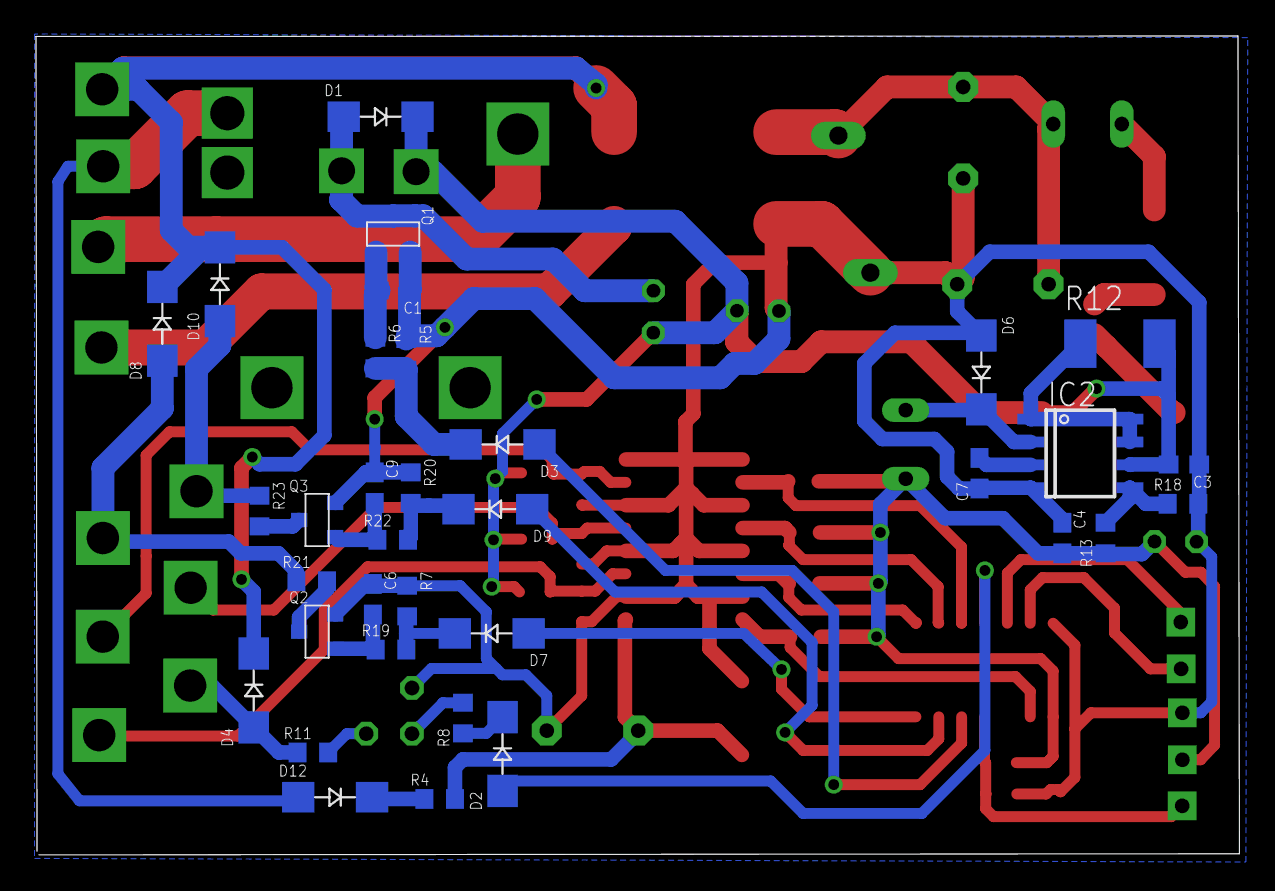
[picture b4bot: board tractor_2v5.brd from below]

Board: 2 copper layers, 66.9 x 45.5 mm, 80 parts (34 on the bottom side), 46 nets.

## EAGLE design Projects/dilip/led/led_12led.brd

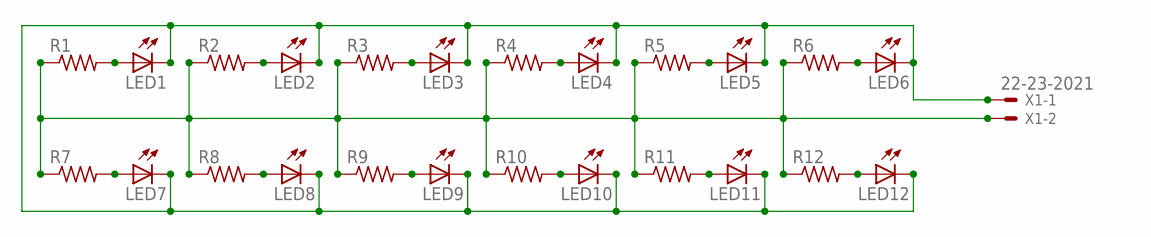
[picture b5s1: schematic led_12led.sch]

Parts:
LED1, LED2, LED3, LED4, LED5, LED6, LED7, LED8, LED9, LED10, LED11, LED12: LED3MM
R1, R2, R3, R4, R5, R6, R7, R8, R9, R10, R11, R12: R-US_0309/12; 0309/12
X1: 22-23-2021

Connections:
unnamed: R1.1, R2.1, R3.1, R4.1, R5.1, R6.1, R7.1, R8.1, R9.1, R10.1, R11.1, R12.1, X1.2
unnamed: LED1.A, R1.2
unnamed: LED2.A, R2.2
unnamed: LED3.A, R3.2
unnamed: LED4.A, R4.2
unnamed: LED5.A, R5.2
unnamed: LED6.A, R6.2
unnamed: LED7.A, R7.2
unnamed: LED8.A, R8.2
unnamed: LED9.A, R9.2
unnamed: LED10.A, R10.2
unnamed: LED11.A, R11.2
unnamed: LED12.A, R12.2
unnamed: LED1.K (C), LED2.K (C), LED3.K (C), LED4.K (C), LED5.K (C), LED6.K (C), LED7.K (C), LED8.K (C), LED9.K (C), LED10.K (C), LED11.K (C), LED12.K (C), X1.1

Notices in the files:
Projects/tractor_panel/source_code/Mplab/v1/mcc_generated_files/pin_manager.h:
(c) 2018 Microchip Technology Inc. and its subsidiaries.
